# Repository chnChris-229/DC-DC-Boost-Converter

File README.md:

# LM2577 DC-DC Boost Converter

A custom DC-DC boost converter designed in KiCad using the LM2577-ADJ switching regulator.

The circuit is designed to step a **9 V input** up to approximately **20 V output**. This project covers the full PCB design process, including schematic capture, component selection, PCB layout, routing, copper pours, design-rule checking, and Gerber/drill file generation.

## Features

- 9 V input
- Approximately 20 V output
- LM2577-ADJ switching regulator
- 180 µH inductor
- Schottky diode
- Input and output filtering capacitors
- Feedback resistor network
- Two-layer PCB
- Ground copper pour
- Through-hole component layout
- Gerber and Excellon drill files generated
- PCB Design Rule Check completed

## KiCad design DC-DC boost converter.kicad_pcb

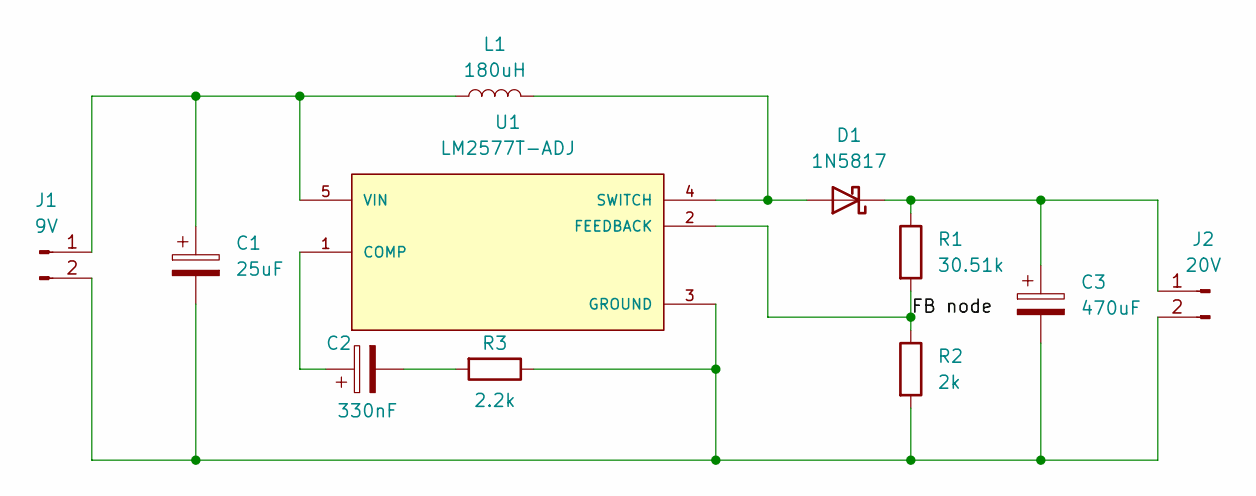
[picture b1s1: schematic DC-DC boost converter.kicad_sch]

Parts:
C1: 25uF; CP_Radial_D6.3mm_P2.50mm
C2: 330nF; C_Disc_D5.0mm_W2.5mm_P5.00mm
C3: 470uF; CP_Radial_D10.0mm_P5.00mm
D1: 1N5817; D_DO-41_SOD81_P10.16mm_Horizontal
J1: 9V; PinHeader_1x02_P2.54mm_Vertical
J2: 20V; PinHeader_1x02_P2.54mm_Vertical
L1: 180uH; L_Radial_D10.0mm_P5.00mm_Fastron_07P
R1: 30.51k; R_Axial_DIN0207_L6.3mm_D2.5mm_P7.62mm_Horizontal
R2: 2k; R_Axial_DIN0207_L6.3mm_D2.5mm_P7.62mm_Horizontal
R3: 2.2k; R_Axial_DIN0207_L6.3mm_D2.5mm_P7.62mm_Horizontal
U1: LM2577T-ADJ; TO-220-5_P3.4x3.7mm_StaggerOdd_Lead3.8mm_Vertical; PARTREV D

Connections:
/FB node: R1.2, R2.1, U1.2 (FEEDBACK)
unnamed: C2.2, R3.2
unnamed: D1.2 (A), L1.2, U1.4 (SWITCH)
unnamed: C3.1, D1.1 (K), J2.1, R1.1
unnamed: C1.1, J1.1, L1.1, U1.5 (VIN)
unnamed: C1.2, C3.2, J1.2, J2.2, R2.2, R3.1, U1.3 (GROUND)
unnamed: C2.1, U1.1 (COMP)

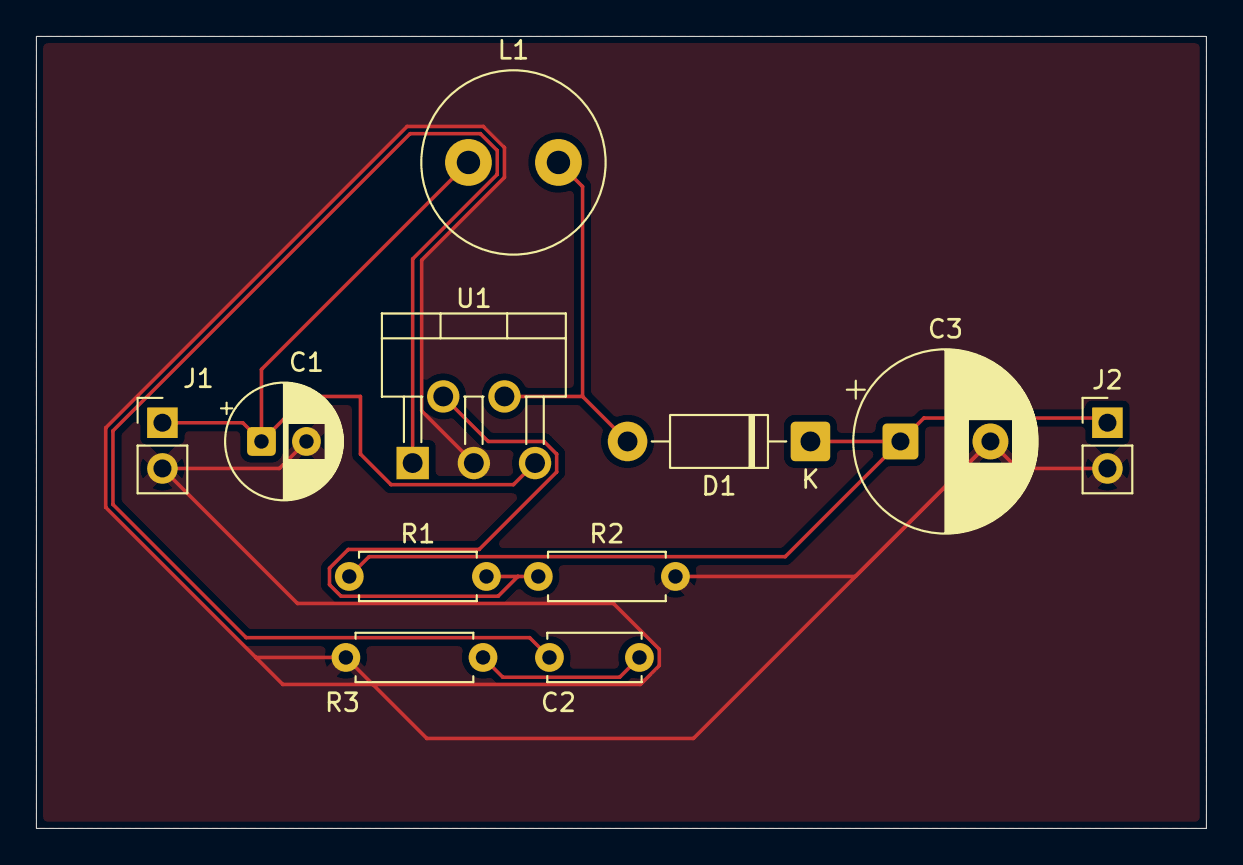
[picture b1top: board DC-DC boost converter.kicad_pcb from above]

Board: 2 copper layers, 65.0 x 44.0 mm, 11 parts (0 on the bottom side), 7 nets.
